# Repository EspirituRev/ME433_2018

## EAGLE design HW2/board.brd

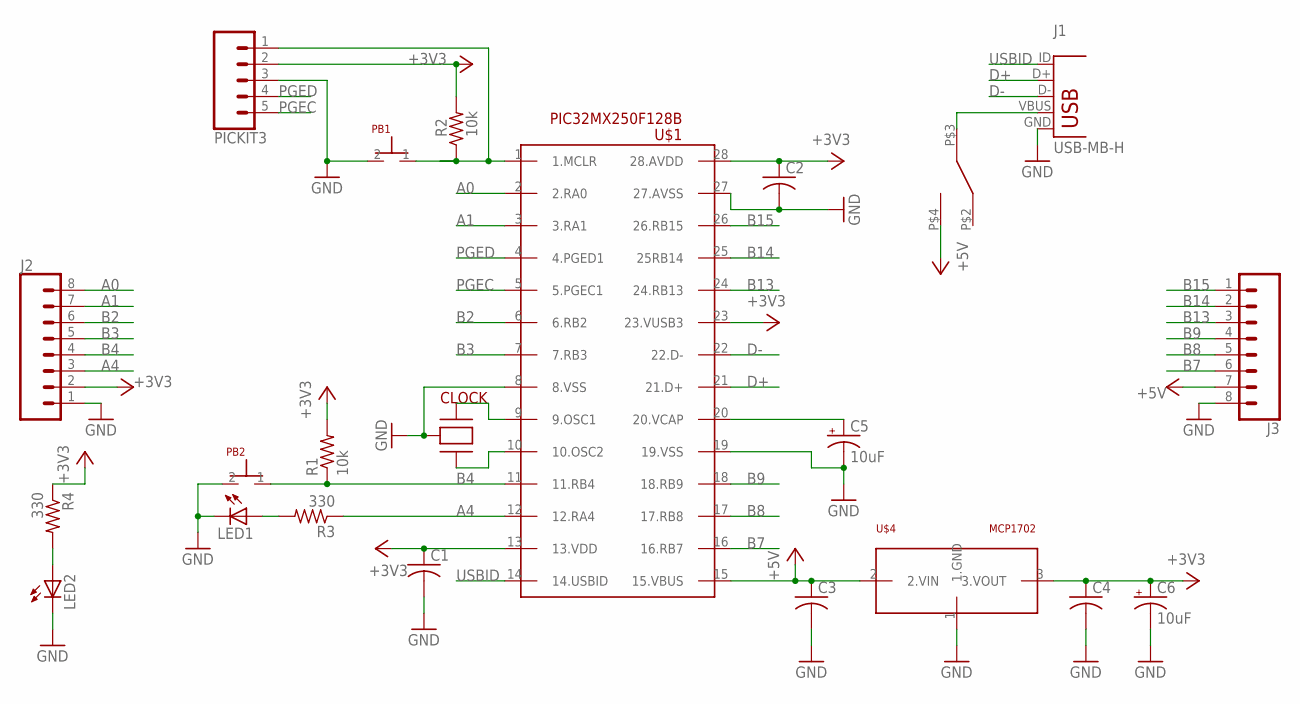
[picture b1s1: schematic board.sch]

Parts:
C1, C2, C3, C4: C-US025-024X044; C025-024X044
C5, C6: 10uF; B45181A
CLOCK: CLOCK
J1: USB-MB-H
J2, J3: CONN_08"; 1X08
LED1, LED2: LED3MM
PB1, PB2: PBUTTON
PICKIT3: CONN_05; 1X05
R1, R2: 10k; 0204/7
R3, R4: 330; 0204/7
U$1: PIC32MX250F128B; DIL28-3
U$2: SWITCH
U$4: MCP1702; TO92

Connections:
+3V3: C1.1, C2.1, C4.1, C6.+, J2.2, PICKIT3.2, R1.2, R2.2, R4.1, U$1.13 (13.VDD), U$1.23 (23.VUSB3), U$1.28 (28.AVDD), U$4.3 (3.VOUT)
+5V: C3.1, J3.7, U$1.15 (15.VBUS), U$2.P$4 (4.OUT2), U$4.2 (2.VIN)
A0: J2.8, U$1.2 (2.RA0)
A1: J2.7, U$1.3 (3.RA1)
A4: J2.3, R3.1, U$1.12 (12.RA4)
B2: J2.6, U$1.6 (6.RB2)
B3: J2.5, U$1.7 (7.RB3)
B4: J2.4, PB2.1 (PIN1), R1.1, U$1.11 (11.RB4)
B7: J3.6, U$1.16 (16.RB7)
B8: J3.5, U$1.17 (17.RB8)
B9: J3.4, U$1.18 (18.RB9)
B13: J3.3, U$1.24 (24.RB13)
B14: J3.2, U$1.25 (25RB14)
B15: J3.1, U$1.26 (26.RB15)
D+: J1.D+, U$1.21 (21.D+)
D-: J1.D-, U$1.22 (22.D-)
GND: C1.2, C2.2, C3.2, C4.2, C5.-, C6.-, CLOCK.2 (2.GND), J1.GND, J2.1, J3.8, LED1.K (C), LED2.K (C), PB1.2 (PIN2), PB2.2 (PIN2), PICKIT3.3, U$1.8 (8.VSS), U$1.19 (19.VSS), U$1.27 (27.AVSS), U$4.1 (1.GND)
unnamed: PB1.1 (PIN1), PICKIT3.1, R2.1, U$1.1 (1.MCLR)
unnamed: J1.VBUS, U$2.P$3 (3.IN)
unnamed: C5.+, U$1.20 (20.VCAP)
unnamed: CLOCK.1 (1.OSC1), U$1.9 (9.OSC1)
unnamed: CLOCK.3 (3.OSC2), U$1.10 (10.OSC2)
unnamed: LED1.A, R3.2
unnamed: LED2.A, R4.2
PGEC: PICKIT3.5, U$1.5 (5.PGEC1)
PGED: PICKIT3.4, U$1.4 (4.PGED1)
USBID: J1.ID, U$1.14 (14.USBID)

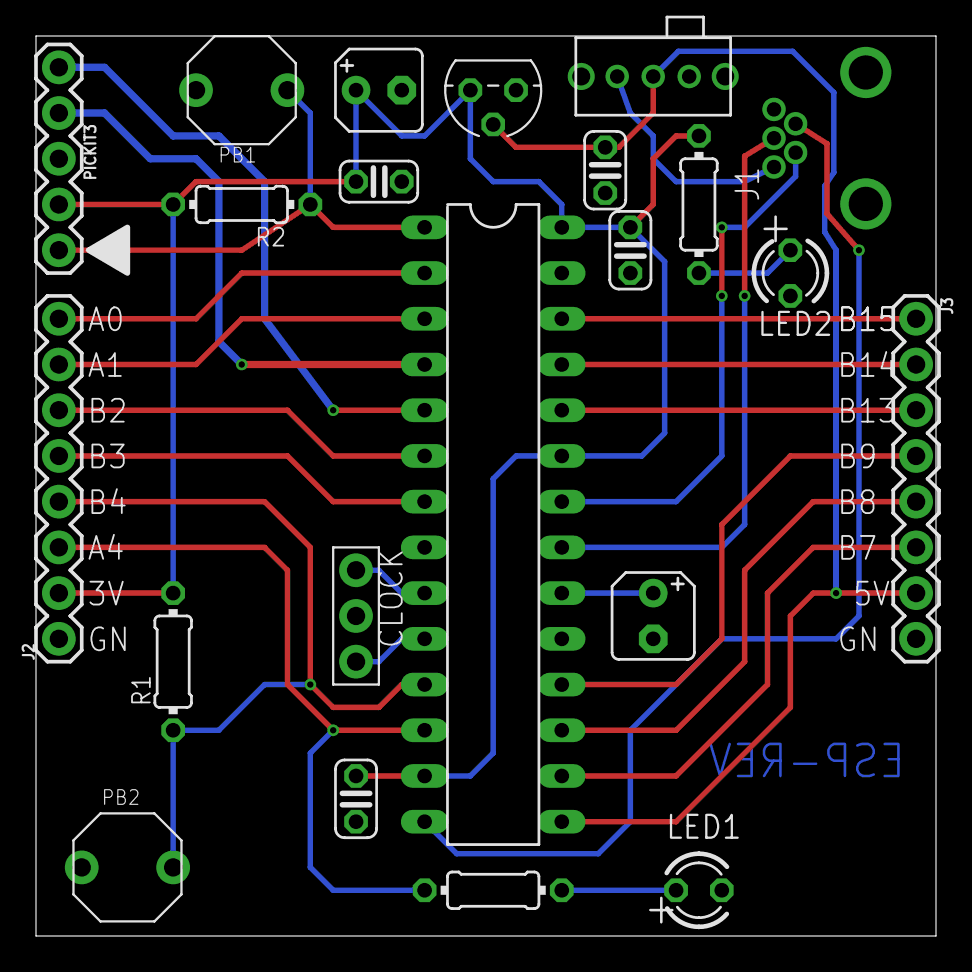
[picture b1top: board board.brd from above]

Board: 2 copper layers, 50.0 x 50.0 mm, 22 parts (0 on the bottom side), 27 nets.

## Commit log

2018-04-10 final
2018-04-10 video
2018-04-12 board try01
2018-04-15 board to check
2018-04-16 para imprimir
2018-04-16 test
2018-04-19 to test SPI
2018-04-22 woroksonly change
2018-04-22 Final SPI
2018-04-24 HW5 ready
2018-04-25 LCD first steps
2018-04-25 write letter
2018-04-25 write hello world
2018-04-25 Com LCD completa
2018-04-25 video LCD
2018-04-29 I2C with imu
2018-04-30 imu works
2018-05-01 Harmony done
2018-05-08 usb com working
2018-05-08 HW9 done
2018-05-13 Filters without com with matlab
2018-05-15 mouse with trick
2018-05-15 Mouse done with IMU
2018-05-17 helloworld
2018-05-17 HW12 done
2018-05-20 camera working
2018-05-23 seekbar added
2018-05-24 Hw14 done
2018-05-27 Filters done
2018-06-09 15 and 16 done
2018-06-09 HW16 done
2018-06-09 HW17 done
2018-06-11 First try
2018-06-12 Slow but works
2018-06-14 Final one
2018-06-14 photo and video
